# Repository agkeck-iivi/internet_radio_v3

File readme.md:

# Internet radio v3

# this archive is now historical.  Active development is moved to https://codeberg.org/agkeck/internet_radio_v3

## hardware

* ESP32s3 DevkitC N8R8
* [adafruit pcm5122 audio board](https://learn.adafruit.com/adafruit-pcm5122-i2s-dac/)
*

### prototype

### schematic

### build

**Version 1**

**Version 2**

**Version 3**

## software

### version 3 software highlights

Version 3 represents a significant refinement in performance, power management, and hardware integration. Key changes include:

* **Audio Hardware Migration**: Moved from the ES8388 codec to the high-performance **PCM5122 DAC**. This included implementing logarithmic volume scaling for a natural listening experience and custom digital ramp rates for glitch-free transitions.
* **Boot Speed Optimization (Fast Connect)**: Cold boot time was reduced from ~21 seconds to **~6 seconds** by implementing WiFi state persistence in NVS. The system now caches BSSID, channel, IP, and DNS settings to bypass discovery and DHCP phases.
* **Advanced Power Management**: Introduced a configurable power-saving strategy supporting **Light Sleep** and **Deep Sleep** transitions. This includes robust watchdog protection to prevent system hangs during sleep-state changes.
* **Dedicated IR Component**: Extracted Bose IR protocol logic into a reusable `ir_remote` component. The system now automatically synchronizes external audio power states during the device's boot and sleep cycles.
* **UI & Observability**: Refined the LVGL interface with a queue-based thread-safety pattern, real-time throughput tracking (kb/s), and custom graphical indicators (e.g., specialized mute glyphs).
* **Web Configuration**: Introduced a web interface for managing device settings (Analog/Digital attenuation, Power Save modes) with immediate runtime application.
* **NVS Configuration Persistence**: All application settings are now persisted to NVS using individual keys, ensuring backward compatibility and state retention across reboots.
* **Stability & Cleanup**: Factored all hardware assignments into a central GPIO header, implemented spurious encoder signal blanking on wakeup, and aligned the project with **ESP-IDF v5.4.3**.

### audio pipeline

The audio pipeline is virtually the same as in version 1.  We added an accumulator to count the bytes read from the http stream and a periodic task to calculate/update the bitrate display on the screen.  This task calculates a 10 second weighted average of one second bitrates.  When this weighted average is 0 we know that we have not received data for 10 seconds.  We use this signal along with a delay of 15 seconds to determine if we need to reboot the device.  If we have not received data for 10 seconds and we are at least 15 seconds since last boot we reboot the device.

### audio board

In Version 3, the radio migrated from the ES8388 (legacy LyraT design) to the high-performance **PCM5122 DAC** (Adafruit board).

The PCM5122 integration features:

* **Custom Driver**: A dedicated driver implementation that adheres to ESP-ADF conventions while providing low-level register control.
* **Analog Gain Control**: To manage the high output levels of the PCM5122, we implemented a 6 dB reduction in the analog gain stage (Page 1, Register 2).
* **Logarithmic Volume Scaling**: Volume settings (0-100) are mapped logarithmically to the DAC's digital volume registers to provide a natural, linear-sounding response to the user.
* **Attenuation Considerations**: Despite the 6 dB analog reduction, the output remains quite loud. Further digital or analog attenuation may be required in future revisions to better align the volume range with typical AUX-input sensitivities.

### encoders

The hardware pulse counters track the position of the encoders. This device has interupts for pulse thresholds but not for changes in pulse counts.  We use a polling task to check the pulse counts and update the encoder position.  For the volume encoder we clamp the value to the range [0, 100] and arrange the relationship between the pulse count and the [0, 100] range to saturate at the endpoints.  In this way, even if the user turns well past an endpoint the reverse movement will immediately affect the value.

### lvgl

LVGL is used for the display interface. Since LVGL is not thread-safe, we implement a **Queue-based Producer/Consumer pattern** to manage all UI updates safely.

#### Thread Safety & Queue

* **Producer**: Any task (e.g., Wi-Fi events, Encoder Logic) that wants to update the UI creates a `ui_update_message_t` struct. This struct contains an event `type` (enum) and optional `data` (int or string pointer). This message is sent to `g_ui_queue`.
* **Consumer**: The `process_ui_updates()` function runs in the main loop (or a dedicated UI task). It consumes messages from `g_ui_queue` and performs the actual LVGL API calls (e.g., `lv_label_set_text`, `lv_screen_load`). This ensures all LVGL operations happen in a single context.

#### Screens

The application uses three primary screens:

1. **Home Screen**: The main dashboard showing the Volume Slider, Station Call Sign, Origin, and Bitrate.
2. **Station Selection**: Displays a "Roller" widget allowing the user to scroll through the list of stations.
3. **Message Screen**: A generic, reusable screen with a centered label used for notifications (e.g., "Rebooting", "Provisioning", "IP Address").

#### Messaging

To display a message on the **Message Screen**:

1. **Fixed Messages**: Helper functions like `switch_to_reboot_screen()` send a message type (e.g., `SWITCH_TO_REBOOT_SCREEN`) that triggers the consumer to load the Message Screen and set a hardcoded string (e.g., "Rebooting").
2. **Arbitrary Messages**: To display dynamic text (like an IP address), the system uses the `UPDATE_IP_LABEL` message type.
    * The producer sends a message with `type = UPDATE_IP_LABEL` and `data.str_value = "My String"`.
    * The consumer reads specific string pointer and updates the label on the Message Screen.
    * *Note: Ensure the string pointer remains valid until processed, or use static/global buffers.*

### wifi

The device relies on Wi-Fi for internet connectivity. If no Wi-Fi credentials are provided (e.g., typically on the first boot), the device enters **Provisioning Mode**.

**Provisioning Mode**:

* The device broadcasts a Bluetooth LE (BLE) service.
* Use the **Espressif BLE Provisioning** app (available on iOS and Android) to connect to the device.
* Follow the app instructions to scan for Wi-Fi networks and provide the SSID and password.
* Once credentials are received, the device will connect to the Wi-Fi network and save the credentials to NVS for future boots.
* **Forced Reprovisioning**: To reset the Wi-Fi credentials and force the device back into provisioning mode, **press and hold the Volume Encoder button** while powering on (or rebooting) the device.

### ir

The Bose Wave radio uses an IR remote control for all functions. Version 2 is designed for this particular unit so we generate our own IR signals to control the radio.  After sniffing the IR signals with ir_nec_transciever project we see that the radio does not use the NEC protocal.  Using 10 samples of the on/off button and 10 samples of the aux button we create a concensus signal for each message. The colab: `bose_sig_analysis.ipynb` shows the analysis of the IR signals.

The bose IR protocal is stateful: the on/off button performs different functions based on the state of the radio.  The aux button is stateless, this signal will always result in the radio being on with input from the aux jack.  Therefore we use aux as the on signal and aux + on/off as the off signal.  We send aux during the boot sequence to ensure that the radio is on when we boot.  We expect the user to double click the volume encoder to turn the radio off.

### nvs

The system uses Non-Volatile Storage (NVS) to persist all critical states and settings:

* **Application Settings**: Analog and Digital attenuation, Power Save mode, sleep delays, and IR transmitter status.
* **Device State**: Current volume level, mute status, and the last selected station index.
* **WiFi State**: Cached BSSID, channel, and IP configuration for "Fast Connect" boot optimizations.

Settings are stored under the `app_config` namespace using individual keys for robust schema evolution.

### application configuration

The radio provides a web interface and a JSON API for real-time configuration. Access the interface at `http://<ESP32_IP_ADDRESS>/config`.

#### Configuration Parameters

| Parameter | Key | Values | Description |
| :--- | :--- | :--- | :--- |
| **Analog Attenuation** | `analog_attenuation` | `0` (0dB), `1` (-6dB) | Hardware gain stage control. |
| **Digital Attenuation** | `digital_attenuation` | `0, 6, 12, ..., 48` | Digital signal scaling after hardware gain. |
| **Power Save Mode** | `power_save_mode` | `0` (None), `1` (Light), `2` (Deep) | Sleep strategy selection. |
| **Light Sleep Delay** | `light_sleep_delay_ms` | Milliseconds | Timeout to enter Light Sleep. |
| **Deep Sleep Delay** | `deep_sleep_delay_ms` | Milliseconds | Additional timeout to move from Light to Deep Sleep. |
| **IR Remote Control** | `ir_protocol` | `0` (None), `1` (Bose Wave), `2` (Dubas Radio) | IR remote protocol selection. |

#### API Access

* **GET `/api/config`**: Returns the current application configuration.
* **POST `/api/config`**: Updates the configuration immediately. Changes are persisted to NVS.

Example update with all parameters:

```bash
curl -X POST -H "Content-Type: application/json" \
     -d '{
       "analog_attenuation": 1,
       "digital_attenuation": 12,
       "power_save_mode": 2,
       "light_sleep_delay_ms": 30000,
       "deep_sleep_delay_ms": 60000,
       "ir_protocol": 1
     }' \
     http://<ESP32_IP_ADDRESS>/api/config
```

Initial station data is stored in a constant array.  On first boot, if the spiffs is not initialized we create a default station json file based on the constant array.  Thereafter, on boot the spiffs should be found and the json file serves as the source of truth for station data.  We provide an API to load the station data from the json file and save the station data to the json file.

To download the current stations:

```bash
curl http://<ESP32_IP_ADDRESS>/api/stations -o stations.json
```

To update the stations:

```bash
curl -X POST -H "Content-Type: application/json" -d @stations.json http://<ESP32_IP_ADDRESS>/api/stations
```

where the codec enum uses these values:

0: MP3
1: AAC
2: OGG
3: FLAC

For help finding stream URIs and codecs for your favorite stations, see the [Station Discovery Guide](station_discovery.md).

### web update to station data

We provide a web interface to update the station data at <ESP32_IP_ADDRESS>/api/stations (or just <ESP_IP_ADDRESS> where there is a link to station data.)  From the web interface we can add, remove, and update station data as well a reorder the list of stations.  The station data is saved to the spiffs and a reboot will apply the changes.

## power management

The radio implements a multi-stage power-saving strategy to minimize energy consumption when idle.

*Note: In local tests setting the router's default dns server to 8.8.8.8  (google dns) or 1.1.1.1 (cloudflare dns) results in faster wakeup times.*

### Power Requirements Table

The following table outlines the current draw and estimated annual energy costs for each operational state. Estimates assume 24/7 operation in the specified state and an electricity cost of **$0.15 per kWh**.

| State | Current (mA) | Power (W) | Annual Energy (kWh) | Annual Cost ($)* |
| :--- | :--- | :--- | :--- | :--- |
| **None (Active)** | 190 | 0.95 | 8.32 | $1.25 |
| **Light Sleep** | 18 | 0.09 | 0.79 | $0.12 |
| **Deep Sleep** | ~8 (est.)† | 0.04 | 0.35 | $0.05 |

*\*Costs are rounded to the nearest cent.*
*†Deep sleep current is dominated by the DevKitC's onboard LDO quiescent current (~5mA) and Power LED (~3mA), as the ESP32-S3 chip itself draws <100µA in this state.*

#### Sleep States

* **Light Sleep**: Entered after a period of inactivity while muted. The CPU state is preserved, and the **SSD1306 screen is automatically powered off** to save energy. The system can be woken by either encoder button.
* **Deep Sleep**: Entered after an extended period in light sleep (if configured). The system performs a full power-down. **Only the Station button (GPIO 6)** can wake the device from this state.
* **IR Sync**: If enabled, the system automatically sends a "Power Off" IR command to the Bose radio when entering sleep, and a "Power On" command when waking.

## operation

The radio's user interface is driven by two rotary encoders, each equipped with an integrated push button (switch).

### Control Summary Table

| Control | Action | Function |
| :--- | :--- | :--- |
| **Volume Encoder** | Rotation | Adjust volume (0-100); Auto-unmutes if turned |
| | Single Click | Toggle Mute/Unmute; **Wake from Light Sleep** |
| | Double Click | Send **Bose ON/OFF** IR command |
| | **Hold at Boot** | **Force Reprovisioning** (Wipe Wi-Fi credentials) |
| **Station Encoder** | Rotation | Scroll through stations; Selects after 2s inactivity |
| | Short Press | Display **IP Address** (3s); **Wake from Mute/Sleep** |
| | Long Press (>1.5s) | **Reboot** device |

---

### Detailed Usage

#### Volume Encoder (Left)

* **Rotation**: Sets the volume level between 0 and 100.
  * The volume is saved to NVS and persists across reboots.
  * If the device is muted, any rotation will automatically restore the previous volume plus or minus the rotation delta.
* **Single Click**: Toggles the mute state.
  * **Wakeup**: If the device is in **Light Sleep**, clicking this button will wake the system and automatically unmute the audio.
* **Double Click**: Triggers the IR transmitter to send a power toggle command to the connected Bose system.
* **Boot Action**: Holding this button during power-on or reset will trigger `wifi_prov_mgr_reset_provisioning()`, allowing you to connect a new Wi-Fi network via BLE.

#### Station Encoder (Right)

* **Rotation**: Navigates the station list.
  * Turning the knob switches the display to the **Station Selection** screen.
  * **Auto-Selection**: Once you stop turning, the radio waits for **2 seconds** before committing the change, switching the stream, and returning to the Home screen.
* **Short Press**:
  * **Normal Mode**: Briefly switches the screen to show the current IP address.
  * **Mute/Sleep Mode**: If the device is muted or in **Light Sleep**, this button acts as a "Wake" key, restoring the audio immediately.
  * **Deep Sleep Wakeup**: This is the **primary wakeup button** for Deep Sleep. Because GPIO 6 is an RTC-capable pin, it is used to bring the system back from a deep sleep state (performing a full reboot).
* **Long Press**: Holding for more than 1.5 seconds triggers an immediate system reboot.

## Bugs

* Between the prototype and the first board we moved the volume button to gpio 42 to facilitate traces on the PCB.  Unfortunately we forgot that gpio 42 is not an RTC GPIO pin.  As a result, the volume button cannot wake the device from deep sleep.  We moved the wakeup function to the station button (gpio 6) and that works fine.  Currently volume turns it off and station turns it on.  We'll see how that works for us.

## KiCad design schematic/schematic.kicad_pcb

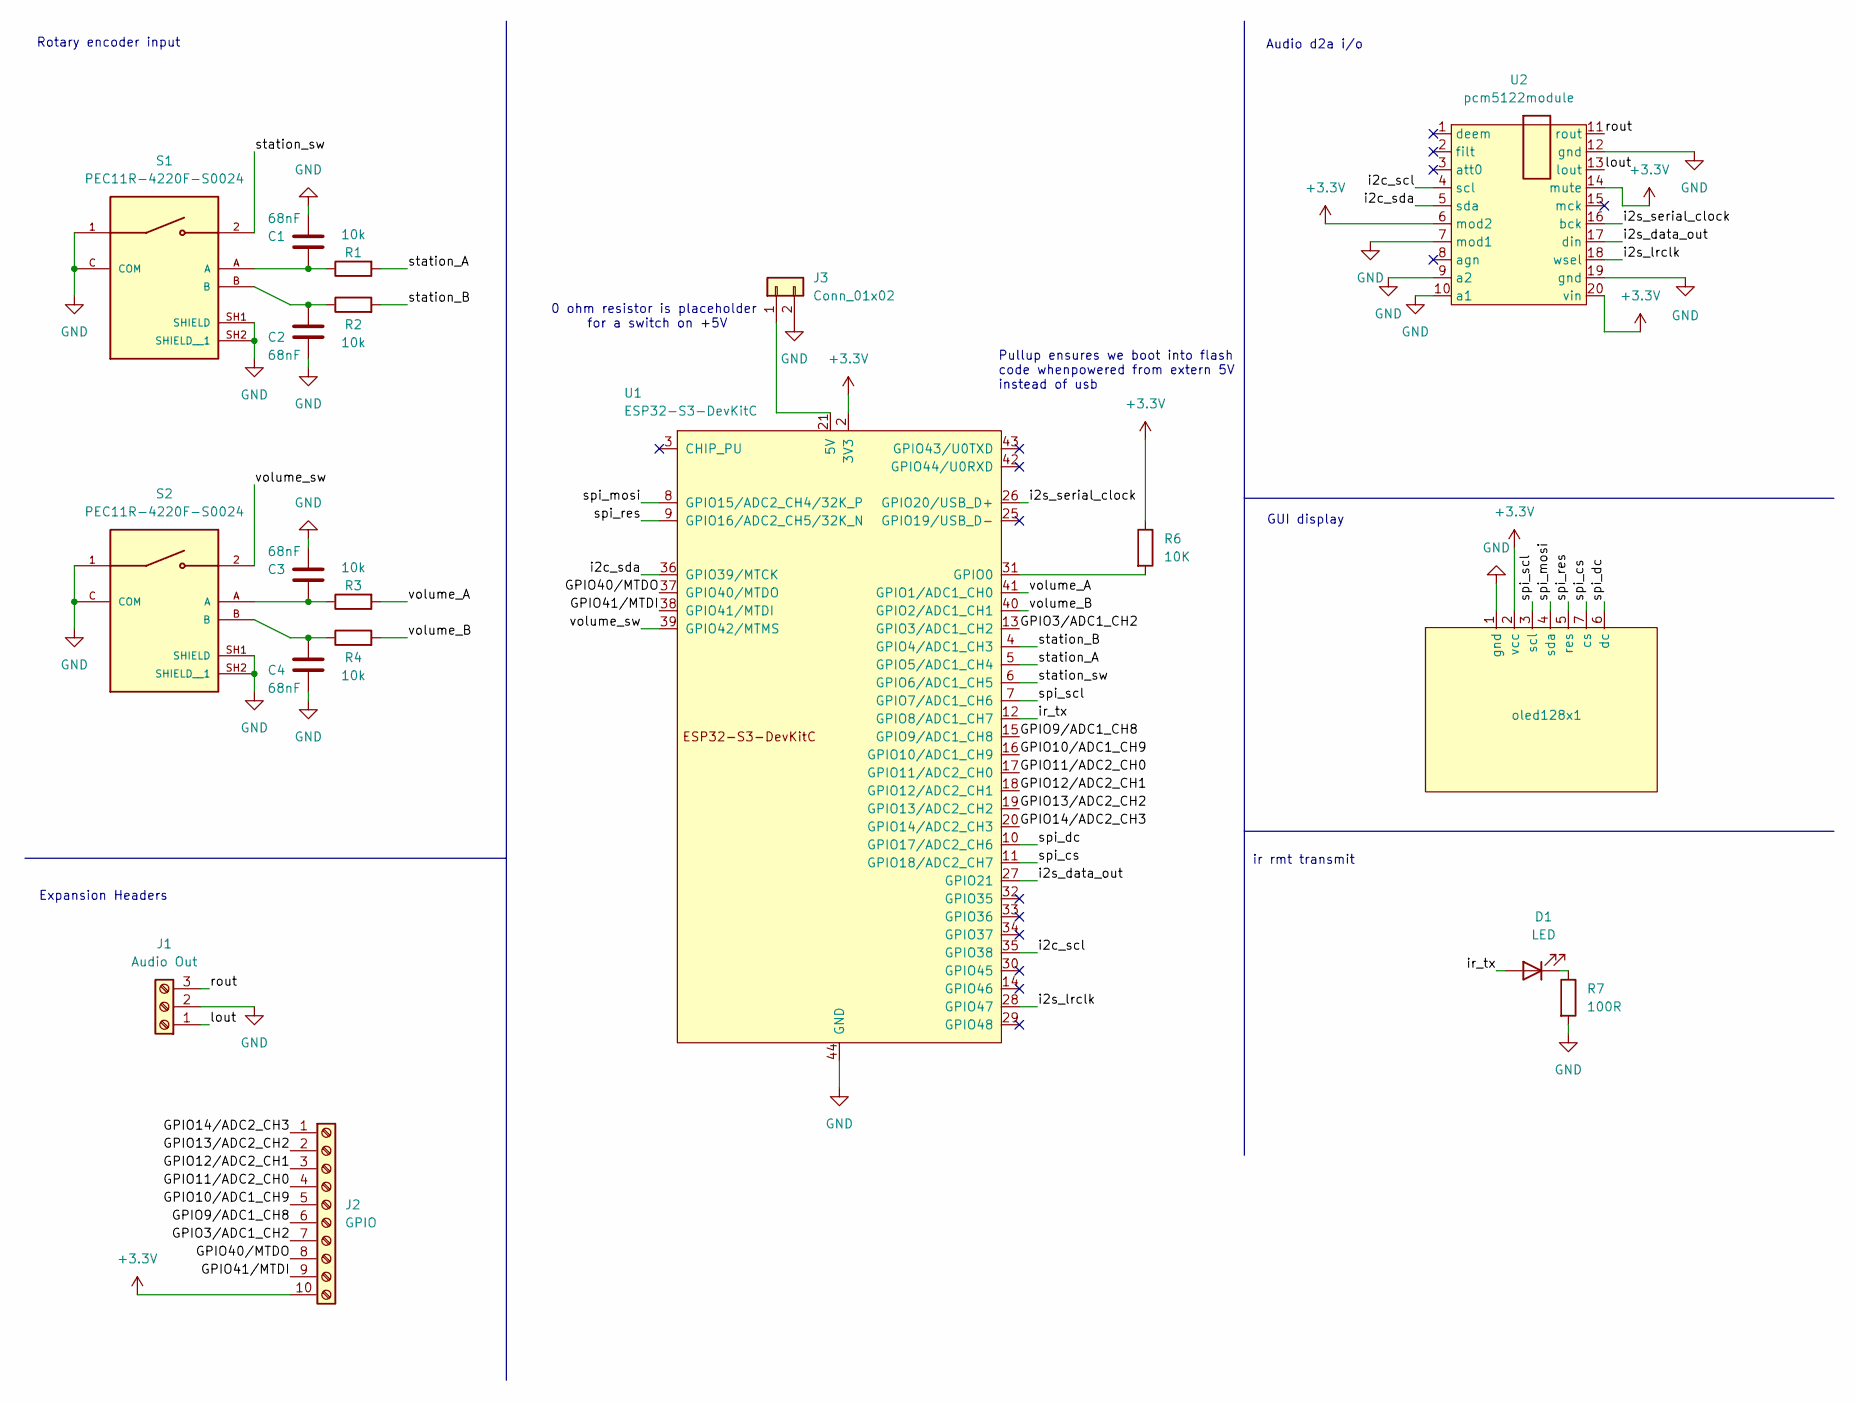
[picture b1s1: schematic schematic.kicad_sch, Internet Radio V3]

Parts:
C1, C2, C3, C4: 68nF; C_0805_2012Metric_Pad1.18x1.45mm_HandSolder
D1: LED; LED_D3.0mm_IRGrey
J1: Audio Out; TerminalBlock_Xinya_XY308-2.54-3P_1x03_P2.54mm_Horizontal
J2: GPIO; TerminalBlock_Xinya_XY308-2.54-10P_1x10_P2.54mm_Horizontal
J3: Conn_01x02; SolderWire-0.1sqmm_1x02_P3.6mm_D0.4mm_OD1mm
R1, R2, R3, R4: 10k; R_0805_2012Metric_Pad1.20x1.40mm_HandSolder
R6: 10K; R_0805_2012Metric_Pad1.20x1.40mm_HandSolder
R7: 100R; R_0805_2012Metric_Pad1.20x1.40mm_HandSolder
S1, S2: PEC11R-4220F-S0024; XDCR_PEC11R-4220F-S0024; PARTREV 11/23
U1: ESP32-S3-DevKitC
U2: pcm5122module; pcm5122_module
oled128x1: oled128x64_spi

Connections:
+3.3V: J2.10, R6.1, U1.1 (3V3), U1.2 (3V3), U2.6 (mod2), U2.14 (mute), U2.20 (vin), oled128x1.2 (vcc)
/GPIO3/ADC1_CH2: J2.7, U1.13 (GPIO3/ADC1_CH2)
/GPIO9/ADC1_CH8: J2.6, U1.15 (GPIO9/ADC1_CH8)
/GPIO10/ADC1_CH9: J2.5, U1.16 (GPIO10/ADC1_CH9)
/GPIO11/ADC2_CH0: J2.4, U1.17 (GPIO11/ADC2_CH0)
/GPIO12/ADC2_CH1: J2.3, U1.18 (GPIO12/ADC2_CH1)
/GPIO13/ADC2_CH2: J2.2, U1.19 (GPIO13/ADC2_CH2)
/GPIO14/ADC2_CH3: J2.1, U1.20 (GPIO14/ADC2_CH3)
/GPIO40/MTDO: J2.8, U1.37 (GPIO40/MTDO)
/GPIO41/MTDI: J2.9, U1.38 (GPIO41/MTDI)
/i2c_scl: U1.35 (GPIO38), U2.4 (scl)
/i2c_sda: U1.36 (GPIO39/MTCK), U2.5 (sda)
/i2s_data_out: U1.27 (GPIO21), U2.17 (din)
/i2s_lrclk: U1.28 (GPIO47), U2.18 (wsel)
/i2s_serial_clock: U1.26 (GPIO20/USB_D+), U2.16 (bck)
/ir_tx: D1.2 (A), U1.12 (GPIO8/ADC1_CH7)
/lout: J1.1, U2.13 (lout)
/rout: J1.3, U2.11 (rout)
/spi_cs: U1.11 (GPIO18/ADC2_CH7), oled128x1.7 (cs)
/spi_dc: U1.10 (GPIO17/ADC2_CH6), oled128x1.6 (dc)
/spi_mosi: U1.8 (GPIO15/ADC2_CH4/32K_P), oled128x1.4 (sda)
/spi_res: U1.9 (GPIO16/ADC2_CH5/32K_N), oled128x1.5 (res)
/spi_scl: U1.7 (GPIO7/ADC1_CH6), oled128x1.3 (scl)
/station_A: R1.2, U1.5 (GPIO5/ADC1_CH4)
/station_B: R2.2, U1.4 (GPIO4/ADC1_CH3)
/station_sw: S1.2, U1.6 (GPIO6/ADC1_CH5)
/volume_A: R3.2, U1.41 (GPIO1/ADC1_CH0)
/volume_B: R4.2, U1.40 (GPIO2/ADC1_CH1)
/volume_sw: S2.2, U1.39 (GPIO42/MTMS)
GND: C1.2, C2.2, C3.2, C4.2, J1.2, J3.2, R7.2, S1.1, S1.C (COM), S1.SH1 (SHIELD), S1.SH2 (SHIELD__1), S2.1, S2.C (COM), S2.SH1 (SHIELD), S2.SH2 (SHIELD__1), U1.22 (GND), U1.23 (GND), U1.24 (GND), U1.44 (GND), U2.7 (mod1), U2.9 (a2), U2.10 (a1), U2.12 (gnd), U2.19 (gnd), oled128x1.1 (gnd)
unnamed: C1.1, R1.1, S1.A
unnamed: C2.1, R2.1, S1.B
unnamed: C3.1, R3.1, S2.A
unnamed: C4.1, R4.1, S2.B
unnamed: D1.1 (K), R7.1
unnamed: J3.1, U1.21 (5V)
unnamed: R6.2, U1.31 (GPIO0)

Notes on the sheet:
GUI display
0 ohm resistor is placeholder for a switch on +5V
Rotary encoder input
Audio d2a i/o
ir rmt transmit
Pullup ensures we boot into flash code whenpowered from extern 5V instead of usb
Expansion Headers

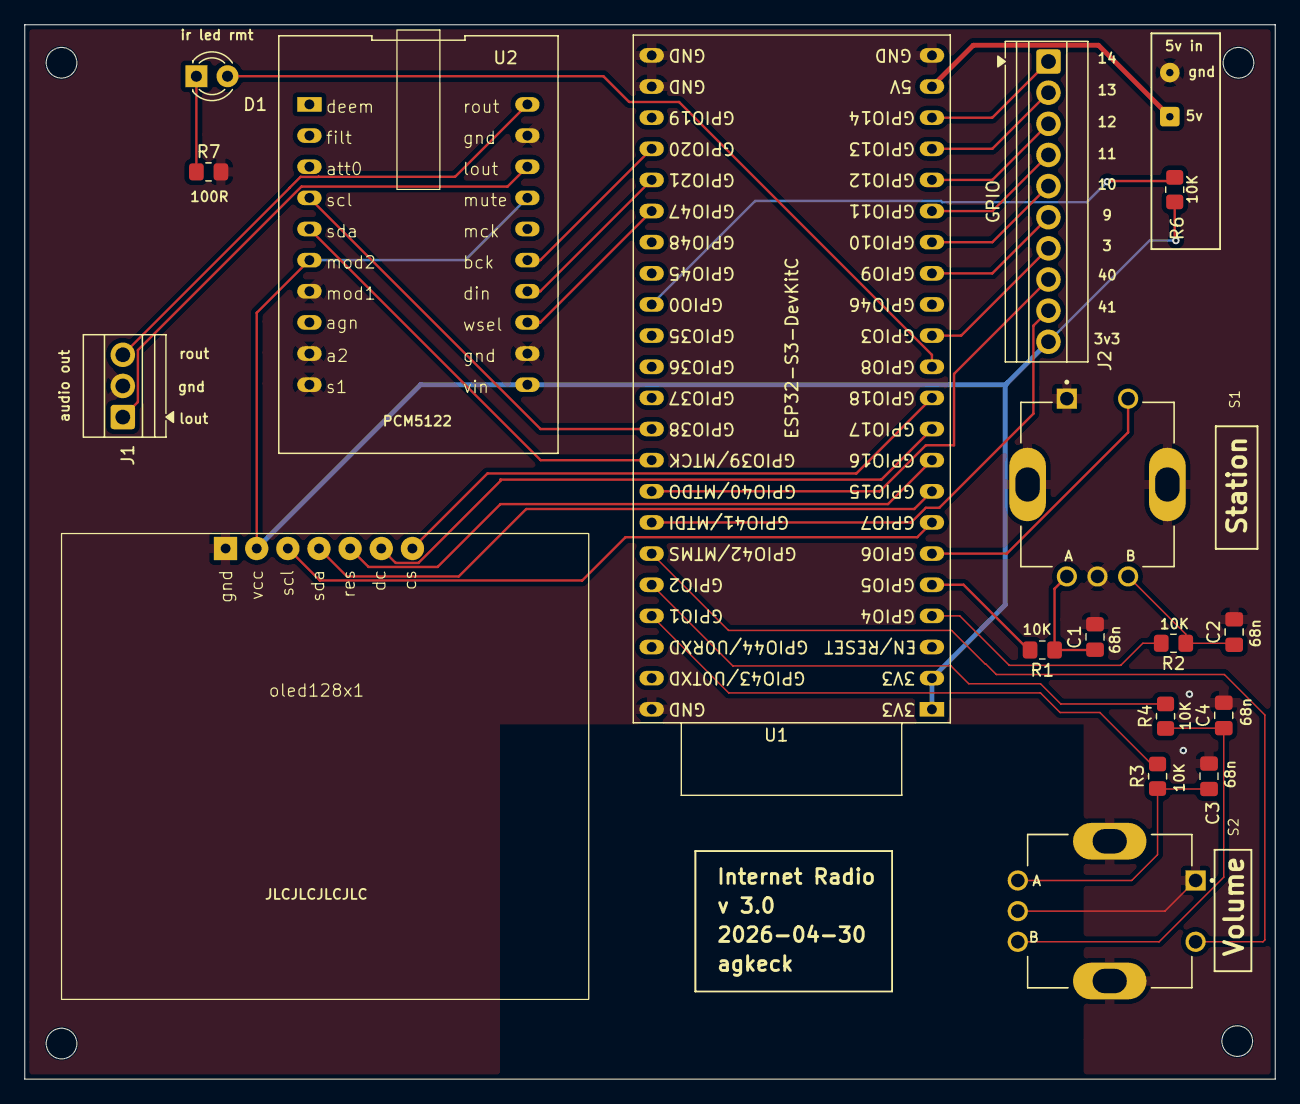
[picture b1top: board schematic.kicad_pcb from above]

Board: 2 copper layers, 102.0 x 86.0 mm, 19 parts (0 on the bottom side), 37 nets.

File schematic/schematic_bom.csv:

"Reference","Qty","Value","DNP","Exclude from BOM","Exclude from Board","Footprint","Datasheet"
"C1,C2,C3,C4","4","68nF","","","","Capacitor_SMD:C_0805_2012Metric_Pad1.18x1.45mm_HandSolder","~"
"D1","1","LED","","","","LED_THT:LED_D3.0mm_IRGrey","~"
"J1","1","Audio Out","","","","TerminalBlock:TerminalBlock_Xinya_XY308-2.54-3P_1x03_P2.54mm_Horizontal","~"
"J2","1","GPIO","","","","TerminalBlock:TerminalBlock_Xinya_XY308-2.54-10P_1x10_P2.54mm_Horizontal","~"
"J3","1","Conn_01x02","","","","Connector_Wire:SolderWire-0.1sqmm_1x02_P3.6mm_D0.4mm_OD1mm","~"
"oled128x1","1","~","","","","oled128x64_spi:oled128x64_spi",""
"R1,R2,R3,R4","4","10k","","","","Resistor_SMD:R_0805_2012Metric_Pad1.20x1.40mm_HandSolder","~"
"R6","1","10K","","","","Resistor_SMD:R_0805_2012Metric_Pad1.20x1.40mm_HandSolder","~"
"R7","1","100R","","","","Resistor_SMD:R_0805_2012Metric_Pad1.20x1.40mm_HandSolder","~"
"S1,S2","2","PEC11R-4220F-S0024","","","","rotary_encoder:XDCR_PEC11R-4220F-S0024",""
"U1","1","ESP32-S3-DevKitC","","","","PCM_Espressif:ESP32-S3-DevKitC",""
"U2","1","pcm5122module","","","","audio_boards:pcm5122_module",""

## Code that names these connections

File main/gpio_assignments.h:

#ifndef _GPIO_ASSIGNMENTS_H_
#define _GPIO_ASSIGNMENTS_H_

// ==========================================
// I2C BUS (Audio Codec)
// ==========================================
#define I2C_SDA_GPIO 39
#define I2C_SCL_GPIO 38

// ==========================================
// I2S BUS (PCM5122 Audio Codec)
// ==========================================
// #define I2S_MCK_GPIO              16

#define I2S_BCK_GPIO 20      // note that we can't use internal usb.
#define I2S_DATA_OUT_GPIO 21 // Connects to DIN on PCM5122
#define I2S_WS_LRCK_GPIO 47
#define I2S_DATA_IN_GPIO 4 // Unused by DAC, but defined

// ==========================================
// SPI BUS (SSD1306 Display)
// ==========================================
#define DISPLAY_SPI_SCLK_GPIO 7
#define DISPLAY_SPI_MOSI_GPIO 15
#define DISPLAY_SPI_RST_GPIO 16
#define DISPLAY_SPI_DC_GPIO 17
#define DISPLAY_SPI_CS_GPIO 18

// ==========================================
// ENCODERS (Rotary Push Buttons)
// ==========================================
#define VOLUME_ENCODER_A_GPIO 1
#define VOLUME_ENCODER_B_GPIO 2
#define VOLUME_ENCODER_PRESS_GPIO 42

#define STATION_ENCODER_A_GPIO 5
#define STATION_ENCODER_B_GPIO 4
#define STATION_ENCODER_PRESS_GPIO 6

// ==========================================
// IR REMOTE
// ==========================================
#define IR_TX_GPIO 8

#endif // _GPIO_ASSIGNMENTS_H_

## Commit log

2026-02-19 Start version 3: clean out v2 specific readme content
2026-02-20 add link to audio board docs to readme
2026-02-24 Add pullup resistor to gpio 0. This ensures that strapping pin gpio 0 is high when booting from external 5V supply. In breadboard testing this did not affect booting from USB jack.
2026-02-25 Change audio board from es8388 to pcm5122. Keep gpio assignments the same but they should be remapped before pcb layout. Works, but is much too loud
2026-02-25 Added stubs to allow all esp adf drivers to compile. My driver doesn't use these functions.
2026-02-27 Move from es8388 board to pcm5122 board. Interestingly, The adafruit driver (thanks to Limor Fried) was written with assistance from Claude code. I used gemini to read that code and adapt it to esp a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
2026-02-27 Use logarithmic scaling on volume setting for volume register. This allows us to use the 0-100 volume range in a natural way.
2026-02-27 Ensure that the volume is preserved in NVS when the radio is muted and a reboot occurs.
2026-02-27 feat: Add a visible mute indicator 'X' on the volume slider and synchronize its state with mute events.
2026-02-27 feat: Mute audio during station changes to prevent pops and update the mute indicator from 'X' to 'M'.
2026-02-28 feat: Add digital volume ramp rate configuration and control for the PCM5122 DAC.
2026-02-28 Adjusting the mute ramp settings. I tried to make a slower fade in but I can't hear a difference.
2026-03-01 feat: Add configurable analog attenuation and disable volume linkage for PCM5122.
2026-03-01 feat: Implement LVGL monochrome rendering for SSD1306, add WiFi power management functions, and downgrade IDF to 5.4.3. Actually, vscode has been using 5.4.3 but sdkconfig did not reflect that.
2026-03-01 feat: Introduce a global throughput history and reset it when the audio pipeline starts or reconnects. This gives correct readings when a stream is just starting.
2026-03-01 Fixed problem with reawakened wifi connection losing DNS connectivity.
2026-03-02 Added 500ms delay upon wake before encoders are make active. Spurious signals on encoder lines were counted at wake time, this should be stopped now. Updated KOTO url.
2026-03-04 turn off task watchdog timer while in light sleep to avoid triggers.
2026-03-04 moved wake up time to the very start of wakeup to mute spurious encoder events on wakeup.
2026-03-04 feat: Implement robust light-to-deep sleep transition with timer-based light sleep and EXT0 deep sleep wakeup, and update project version.
2026-03-05 created power saving strategy with values none, light sleep, light+deep sleep to control behavior. pulled delays out as variables for eventual configuration via settings page.
2026-03-07 Disable task wdt before light sleep.
2026-03-07 removed testing message
2026-03-08 Add guards to prevent the throughput wdt from advancing during sleep. We destroy the pipeline prior to sleep causing the throughput to drop to zero. If the esp_light_sleep_start() function blocks wai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
2026-03-08 created requirement doc for ir remote component.
2026-03-08 refactor: move IR remote control logic and Bose protocol data into a dedicated component.
2026-03-08 feat: Integrate IR remote audio control with light sleep, reduce light sleep delay, and ensure RMT transmission completion.
2026-03-08 set light sleep delay to 10 seconds to facilitate testing. Don't forget to replace this with 20 minutes for production.
2026-03-10 Factor all gpio assignments out to a single header file for easy prototyping.
2026-03-10 moved gpio_assignments.h to main directory.
2026-03-11 Added sampling frequency to the table of station features.
2026-03-12 Moved wifi reconnect data to RTC safe memory and try that data up reawakeing from deep sleep. This caches IP address and DNS settings. If it work waking from deep sleep should drop below 11 seconds. 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
2026-03-13 Chnged the label on display from KBPS to kb/s. Straight lower case doesn't work since the descender on the 'p' is cut off.
2026-03-13 Change the mute symbol from M to a close window glyph. Also added baseline correction for cases where the middle of the volume bar is too low to show the whole glyph.
2026-03-13 feat: Implement WiFi fast connect using NVS for cached network state and integrate audio pipeline event listener.
2026-03-15 docs: Add Version 3 software highlights, PCM5122 DAC integration details, and a power management table to the README.
2026-03-15 implement digital attenuation.
2026-03-15 Refactored all the runtime configuration definitions into a single app_config .c and .h files
2026-03-15 cleanup comments
2026-03-15 updated sdkconfig from upstream.
2026-03-15 changed digital_attenuation type to enum from in.
2026-03-15 consolidated redundant configuration for ir remote enable. Also, sdkconfig changed again.
2026-03-15 feat: Implement web-based configuration for audio settings and power management, and clean up unused SDK configurations. Configuration is now stored in NVS
2026-03-15 more sdkconfig changes that are either coming from upstream or local ai editing.
2026-03-17 Test with router DNS set to 8.8.8.8 shows significantly faster wake times.
2026-03-18 Removed caching of ip, dns and retrying with cached values upon wake from sleep and deep sleep. Attempting to reimplement with correct esp-idf options.
2026-03-18 formatting
2026-03-19 feat: always compile IR remote component, control functionality via runtime config, and improve BOSE audio off sequence by using the idempotent off sequence (aux to turn on and then toggle on/off to 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
2026-03-19 feat: Implement silent boot for PCM5122 by adding initial hardware mute, refining the initialization sequence, and delaying application-level unmute. This is better than before but still not silent. 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
2026-03-26 Still working on removing pops during boot. Not yet successfull. Here we are more careful with ramp settings.
2026-03-26 removed v2 images.
2026-03-31 Update schematic with note about pullup on GPIO0 for booting from external 5V, bypassing usb.
2026-04-19 refactor: update I2S bus pins and reformat GPIO definitions for consistency. Note that gpio48 is dedicated to the onboard rgb led and so cannot be used for signal.
2026-04-19 docs: add GPIO constraints reference and clarify internal USB pin conflicts in assignments header
2026-04-19 chore: update GPIO pin assignments for I2C bus for better layout. temporarily moved station encoder A to make room.
2026-04-19 Added cad files for laying out the pcb. the .x_t file is proprietary but I was able to conver to .stp for import into kikad using online converter at https://3dencoder.com/XT-to-stp
2026-04-20 Remove gpio assignment for input from 5122 since it is not available.
2026-04-23 moved station encoder and ir_tx gpios.
2026-04-23 Moved spi gpio pin assignments.
2026-04-23 update gpio assignments on schematic.
2026-04-26 moved ir rmt gpio to (perhaps) improve trace routing.
2026-04-28 Assigned footprints and created custom footprints in prepartion for pcb layout.
2026-04-29 Change current limiting resistor to 100R from 33R. Lower power seems to work fine for the ir remote.
2026-04-30 Reordered station encoder gpio assignments for cleaner routing.
2026-04-30 Gitignore transient files involved with schematic and pcb.
2026-04-30 Design PCB.
2026-05-01 Added minimal operating instructions to back silkscreen.
2026-05-01 Reassigned volume encoder pins in order to reroute outside of the esp32 antenna. Also added a keep out zone on both top and bottom around the antenna.
2026-05-01 Expanded keep out zone around antenna. Recommendations suggest 15mm. I am able to keep the ground plane out but there are still three pads and traces in the keep out region. These are related to the 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
2026-05-01 Added rounting for common on volume encoder. The part of the volume encoder in the keep out region was the rotary encoder. Without the ground plane the common was not connected so I added a trace to 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
2026-05-02 Fixed two islands in the front ground plane by adding vias.
2026-05-02 Generated gerbers and bom.
2026-05-12 Updated pdf of schematic.
2026-05-12 moved to kicad 10
2026-05-14 update pcb to kicad 10
2026-05-14 update gitignore to ignore history and lock files associated with kicad
2026-05-14 chore: update .gitignore to exclude additional KiCad schematic artifacts and directories
2026-05-16 Change the default digital attenuation to -3db. This works well with the tivoli audio device.
2026-05-16 enable ir remote by default
2026-05-16 Changed devkit flash to 8M to match the new devkits. It works!
2026-05-16 Added screen off function to ensure that the screen turns off during sleep.
2026-05-16 moved wake up functions to station press. volume switch is on gpio 42 which is not RTC enabled. While not ideal we now press the volume to mute/sleep and station to unmute/wake basically volume for o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
2026-05-17 First draft of gemini generated user manual.
2026-05-17 Added pdf version of user manual. The manual is still pretty bad.
2026-05-17 update readme with images of build and schematic.
2026-05-17 refactored ir remote commands to facilitate supporting multiple protocols. I have not yet exposed this through the configuration page.
2026-05-17 Move KHEN to the top of the station list, update documentation.
2026-05-17 spelling
2026-05-17 increased the polling rate on the volume button to catch very quick clicks. With the new build very quick clicks are easy so this accomodates the new build.
2026-05-18 fixed a problem where wakup from deep sleep did not send audio on ir remote signal.
2026-05-18 feat: trigger IR remote audio power-on when unmuting the device
2026-05-18 feat: add support for DUBAS_RADIO IR protocol and replace boolean toggle with protocol configuration
2026-05-19 Send ir rmt command to turn on radio after the first frame of audio is decoded. This ensures that the high current demands of establishing a connection are mostly done so that the ir led can get full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
2026-05-19 formalized ir_protocol as an enum and set the default to be none.
2026-05-19 fix spelling in schematic.
2026-05-20 moved khen into first position in json file that is written to spiffs.
2026-05-20 update url for KRCL stream
2026-05-20 Corrected KRCL stream url.
2026-05-20 Update documentation
2026-05-21 New ir behavior: audio on when first frame of audio is decoded, regardless of mute state. Audio off when going into light sleep. There is a possibility that upon rebooting from power outage the ir re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
2026-05-22 Add error logging to turn_audio_on() to diagnose occasional ir rmt misses.
2026-05-23 Add 150ms delay for sending the audio_on ir remote command.
2026-05-24 Adjust delay for second ir remote signal.
2026-05-24 Added code to delete and reinitialize the ir rmt peripheral after waking from light sleep.
2026-05-24 Moved ir init later in boot sequence.
2026-05-24 Added images of v1 and v2 builds to readme for comparison.
2026-05-28 removed an unnecessary alias for the ir remote tx gpio assignment.
2026-05-29 General cleanup: removed unused symbols, removed duplicate queue init, removed some debugging comments.
2026-05-30 add a comment on building from command line.
2026-06-01 Added message that development has moved to codeberg.
